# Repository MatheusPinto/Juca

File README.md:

---

---
Juca is an embedded mobile robotics board designed specifically for education. Juca combines affordability, expandability, and robust functionality, making it suitable for classroom and competition environments. Key features include modular hardware akin to Arduino shields, support for differential drive robots, and seamless integration with educational programming platforms.

This repository contains all the resources related to the development of the rover, 
including **firmware**, **software**, and **hardware** (electronics and mechanics). 

## 📂 Repository Structure

-   [docs/](docs/) - Project documentation
    
-   [firmware/](firmware/) - Microcontroller source code
    
-   [software/](software/) - PC applications, scripts, and simulations
    
-   [hardware/](hardware/) - Hardware design files
    
    -   [electronics/](hardware/electronics/) - Electronic design files
        
        -   [kicad/](hardware/electronics/kicad/) - Schematics and PCB layouts (KiCad project files)
            
        -   [bom/](hardware/electronics/bom/) - Bill of Materials
            
    -   [mechanics/](hardware/mechanics/) - Mechanical models (CAD, STL, STEP, drawings)
        
-   [tests/](tests/) - Integration tests (firmware + hardware + software)
    
-   [tools/](tools/) - Utility scripts and helper tools
    
-   [LICENSE](LICENSE) - License file
    
-   [README.md](README.md) - This file

## 📌 Reference

For information on the motivation, design objectives, and development criteria of the robot,  
please refer to the article *“Juca: an embedded mobile robotics board for education”*,  
published in the *16th Workshop on Robotics in Education (WRE 2025)*.

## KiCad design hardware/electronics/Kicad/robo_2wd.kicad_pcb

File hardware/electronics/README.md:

# Projeto Eletrônico do Juca

O Juca é a placa eletrônica propriamente dita, conforme observado na [Figura 1](#juca_board) e [Figura 2](#juca_board_back). Ela possui 180 mm x 125 mm, composta de duas camadas, com objetivo de ser robusta. 

<div id="juca_board" align="center">
  
  <br>
  <i>Figura 1: Visão 3D da parte superior da placa Juca.</i>
</div>

<br><br>

<div id="juca_board_back" align="center">
  
  <br>
  <i>Figura 2: Visão 3D da parte inferior da placa Juca.</i>
</div>

<br><br>

Na [Figura 3](#juca_diagram) é apresentado o diagrama de blocos do Juca. Serão apresentados cada módulo presente no sistema.

<br>

<div id="juca_diagram" align="center">
  
  <br>
  <i>Figura 3: Diagrama de blocos didático do sistema.</i>
</div>

---

## Microcontrolador (SoC)

O sistema utiliza o SoC **ESP32-S3-WROOM-1**, aproveitando suas capacidades de processamento dual-core e capacidade de comunicação por Wi-fi e BLE. O esquemático relacionado a esse módulo encontra-se na [Figura 4](#esp32_s3_sch).
O ESP32-S3 têm picos de consumo de corrente muito rápidos (especialmente ao ligar o Wi-Fi). Os capacitores (C11 e C12) próximos aos pinos de alimentação (`3V3`) filtram ruídos de alta frequência e evitam que a tensão caia momentaneamente, o que causaria resets inesperados.

<br>

<div id="esp32_s3_sch" align="center">
  
  <br>
  <i>Figura 4: Esquemático módulo ESP32-S3-WROOM-1.</i>
</div>

<br><br>

- **R13 (10k Pull-up no EN):** Mantém o pino de Enable (Reset) em nível alto (3.3V) para que o chip opere de maneira normal quando o pushbutton SW1 não for pressionado. O botão SW1, ao ser pressionado, aterra esse pino para resetar a MCU.

- **R14 (10k Pull-down no GPIO45):** Este é um **resistor de configuração (Strapping Pin)**. Ele garante que o pino 45 esteja em 0V durante o boot, informando ao ESP32-S3 que a memória Flash interna opera a **3.3V**. Sem ele, o chip poderia tentar alimentar a memória com 1.8V, impedindo a inicialização.

<br>

Toda gravação de firmware e comunicação com o chip é feita diretamente por meio da interface USB implementada diretamente no ESP32-S3 ([Figura 5](#usb_sch)), através dos pinos GPIO19 (DEBUG_DM) e GPIO20 (DEBUG_DP).

<br>

<div id="usb_sch" align="center">
  
  <br>
  <i>Figura 5: Interface USB de conexão com o ESP32-S3.</i>
</div>

---

## Alimentação

O hardware possui três barramentos principais de alimentação ([Figura 7](#power_sch)):

1.  **+BATT (Potência):** 6V a 12V para os motores e alimentação geral do sistema. Essa alimentação pode advir de uma bateria (por meio do conector J3) ou de uma fonte CC externa conectada por um por jack-cc (J4). Um interruptor (SW3) é responsável por conectar a bateria/fonte ao restante da placa. Se bateria e fonte estiver conectadas no sistema, a fonte externa poderá carregar a bateria. Note que a placa não possui BMS, dessa forma será necessário utilizar no próprio pack de bateria um BMS.

2. **5V (Lógica):** Gerado por um conversor *buck* bastante utilizado em projetos de eletrônica hobistas (Figura) ou pela interface USB ([Figura 6](#buck_il_2825)). Cria uma barramento de 5V para alimentar dispositivos externos, e para alimentar o driver de motor e o sensores ultrassônicos. Se alimentação vier do USB (sem fonte +BATT), o driver de motor é acionado, mas os motores não.

<div id="buck_il_2825" align="center">
  
  <br>
  <i>Figura 6: Mini placa para buck IL 2825.</i>
</div>

<br>

3.  **3.3V (Lógica):** Gerado por um regulador LDO (como o AMS1117) para alimentar o ESP32-S3 e o restantes dos sensores.

<br>

<div id="power_sch" align="center">
  
  <br>
  <i>Figura 7: Módulos de alimentação da placa.</i>
</div>

---
## *Driver* de motores

Para acionamento dos motores por meio do PWM, utilizou-se o chip L298N. Esse módulo possui uma ponte H para controle de direção e amplificação da potência nos motores. Um diagrama do circuito do L298N retirado do seu datasheet é apresentado na [Figura 8](#l298N). O esquemático do driver desenvolvido com o chip é apresentado na [Figura 9](#mot_driver_sch).

<br>

<div id="l298N" align="center">
  
  <br>
  <i>Figura 8: Diagrama do circuito interno do L298N.</i>
</div>

<br><br>

<div id="mot_driver_sch" align="center">
  
  <br>
  <i>Figura 9: Esquemático do circuito driver de motor do Juca.</i>
</div>

<br><br>

A placa foi pensada usando um motor com as seguintes especificações (mas facilmente adaptado para outros tipos de motor, mudando valores de tensão de alimentação da bateria e/ou mudando alguns valores de resistores no circuito de sensor de corrente):

|**Parâmetro**|**Valor / Especificação**|
|---|---|
|**Tensão de Operação**|6V DC|
|**Velocidade (Sem Carga)**|280 RPM|
|**Máxima Eficiência**|2.0 kg.cm @ 170 RPM|
|**Potência na Máx. Eficiência**|2.0 W|
|**Corrente na Máx. Eficiência**|0.60 A|
|**Torque de Partida (Stall)**|5.2 kg.cm @ 110 RPM|
|**Potência Máxima**|3.1 W|
|**Corrente de Pico (Stall)**|1.10 A|
|**Diâmetro do Motor**|25 mm|
|**Comprimento Total (Corpo + Eixo)**|73 mm|
|**Diâmetro do Eixo**|4 mm|
|**Comprimento do Eixo**|12 mm|

<br>

O motor utilizado a priori é daqueles se acham facilmente em lojas online de materiais eletrônicos, possuindo integrado um *encoder* de quadratura a efeito hall, conforme [Figura 10](#motor_wire)

<br>

<div id="motor_wire" align="center">
  
  <br>
  <i>Figura 10: Motor com encoder utilizado.</i>
</div>

<br>

Com base nas combinações dos pinos MOT_IN1, MOT_IN2, MOT_IN3 e MOT_IN4, pode-se determinar o controle de direção e velocidades das rodas. Note que quando todos os pinos estiverem em ALTO, as rodas irão travar eletronicamente, pois as portas lógicas SUPERIORES do driver ([Figura 8](#l298N)) irão forçar os polos do motor ao mesmo potencial elétrico (Vcc). Da mesma forma, quando todos os pinos estiverem em BAIXO, as rodas irão travar eletronicamente, pois as portas lógicas INFERIORES do driver ([Figura 8](#l298N)) irão forçar os polos do motor ao mesmo potencial elétrico (GND). Infelizmente, nesse projeto não há possibilidade de deixar as rodas em ponto morto, sem torque (deixar as rodas desconectadas), pois os pinos de habilitação (EnA e EnB) foram deixadas diretamente conectadas do +3V3.

<br>

| **Direção Desejada**  | **MOT_IN1** | **MOT_IN2** | **MOT_IN3** | **MOT_IN4** | **Efeito Prático**                       |
| --------------------- | ----------- | ----------- | ----------- | ----------- | ---------------------------------------- |
| **Frente**            | PWM         | Low         | PWM         | Low         | Ambas as rodas giram para frente         |
| **Trás**              | Low         | PWM         | Low         | PWM         | Ambas as rodas giram para trás           |
| **Girar p/ Direita**  | PWM         | Low         | Low         | PWM         | Roda esquerda p/ frente, direita p/ trás |
| **Girar p/ Esquerda** | Low         | PWM         | PWM         | Low         | Roda direita p/ frente, esquerda p/ trás |
| **Curva p/ Direita**  | PWM         | Low         | Low         | Low         | Apenas roda esquerda gira                |
| **Curva p/ Esquerda** | Low         | Low         | PWM         | Low         | Apenas roda direita gira                 |
| **Freio (Ativo)**     | Low         | Low         | Low         | Low         | Motores travam eletronicamente           |
| **Freio (Ativo)**     | High        | High        | High        | High        | Motores travam eletronicamente           |

<br>

Além do acionamento dos motores, o módulo de driver de motores fornece a corrente dos motores por meio de dois pinos SENSE_A e SENSE_B. Essas correntes são aplicadas a resistores de *shunt* de 0,1 Ohm PTH do tipo filme de carbono de 2 Watts (no limiar de potência para os motores), por serem fáceis de serem achadas comercialmente no Brasil. Sabendo a resistência dos *shunts* e medindo a tensão dos mesmos por meio de do ADC no SoC, aplica-se a Lei de Ohm e se obtém a corrente.. Posto isto, os valores de queda de tensão que surgem nesses resistores são muito pequenos, devendo ser necessário um circuito de amplificação (que será abordado posteriormente). 

O módulo também possui uma interface para entrada de encoders de quadratura. Essa parte será abordada mais adiante também, pois também serão apresentados os encoders utilizados. 

---
## Sensor de corrente dos motores

Para monitorar a carga dos motores e detectar obstáculos ou travamentos (stall), o projeto utiliza um circuito de amplificação baseado no AmpOp **LM324A** ([Figura 11](#curr_sense_sch)). O circuito utiliza a queda de tensão sobre os resistores de shunt (R1​ e R2​ de 0.1Ω em [Figura 9](#mot_driver_sch)) localizados nos pinos de _Sense_ do driver L298N. Como essa tensão é muito baixa para uma leitura precisa pelo ADC, aplicamos um **Amplificador Não-Inversor** a cada uma delas.

<br>

<div id="curr_sense_sch" align="center">
  
  <br>
  <i>Figura 11: Esquemático do circuito de medição de corrente dos motores.</i>
</div>

<br><br>

O ganho dos amplificadores foi determinado de tal forma que a corrente máxima de torque dos motores que foram utilizados (1,1 A) fosse próxima dos 3 V, já que o ADC do ESP32-S3 possui fundo de escala de 3V3. Como o LM324 não é rail-to-rail, ele satura cerca de 1.5V abaixo do VCC​, com 5V de alimentação, a saída máxima real será de aproximadamente **3.5V**. o suficiente para a aplicação. Para tanto, o cálculo usando o amplificador não inversor foi:

$$G=1+R_{in}​.R_{feedback​}​=1+3k.82k​≈28,33.$$

<br>
Abaixo está uma tabela ilustrativa com exemplos de tensão e leitura do ADC.
<br>

| **Corrente do Motor** | **Tensão no Shunt** | **Saída do AmpOp** | **Valor no ADC (10-bit)** | **Status do Motor** |
| --------------------- | ------------------- | ------------------ | ------------------------- | ------------------- |
| $0.1\text{A}$         | $0.01\text{V}$      | $0.28\text{V}$     | $\approx 87$              | Sem carga           |
| $0.6\text{A}$         | $0.06\text{V}$      | $1.70\text{V}$     | $\approx 527$             | Eficiência Máxima   |
| **$1.1\text{A}$**     | **$0.11\text{V}$**  | **$3.11\text{V}$** | **$\approx 965$**         | **Stall (Travado)** |
<br>
Na saída do amplificador é colocado um filtro passa-baixa RC (150Ω e 1μF) para eliminar ruídos de chaveamento (PWM), e um diodo Zener de 3.3V para garantir que a saída nunca ultrapasse o limite do pino analógico do microcontrolador.

---
## *Encoders*

O Juca é capaz de receber os dois sinais advindos de um encoder incremental de quadratura. Isso é importante no cálculo de odometria do robô, onde é possível determinar o deslocamento angular da roda com base nos pulsos dos sinais gerados pelo encoder.

O encoder é acoplado à roda, que possui algum tipo de disco magnético (ou óptico) multi-polar que gira solidário ao eixo do motor.

Os sinais gerados pelo encoder são geralmente denominados Fase A e Fase B. De forma básica, existem dois sensores que medem a variação do campo magnético (ou a passagem de luz) e geram ondas quadradas defasadas entre si em 90°. Essa defasagem é o que permite ao sistema identificar não apenas a velocidade, mas também o sentido de rotação (horário ou anti-horário), dependendo de qual fase sofre a transição de nível primeiro (ver [Figura 12](#quad_enc_anima) e [Figura 13](#encoder_wave)).

<br><br>

<div id="quad_enc_anima" align="center">
  
  <br>
  <i>Figura 12: Ilustração do comportamento de um encoder de quadratura.</i>
</div>

<br>

<div id="encoder_wave" align="center">
  
  <br>
  <i>Figura 13: Comportamento do encoder para o sentido direto e reverso da roda.</i>
</div>

<br>
<br>

O encoder utilizado primariamente no Juca é o do motor apresentado na [Figura 10](#motor_wire), e possui os seguintes parâmetros:

| **Parâmetro**            | **Detalhe / Valor**                      |
| ------------------------ | ---------------------------------------- |
| **Relação de Redução**   | 1:34 (Exato: 1:34.02)                    |
| **Resolução do Encoder** | 341.2 PPR (Pulsos por Revolução da Roda) |
| **Cálculo da Resolução** | 11 pulsos (motor) x 34.02 (redução)      |
| **Comprimento Total**    | 73 mm (incluindo motor e eixo)           |

O motor elétrico gira muito rápido, mas com pouca força (torque). Por isso, ele possui uma **caixa de engrenagens** acoplada.

- **O que significa:** O motor interno precisa dar **34,02 voltas** completas para que a roda do robô dê apenas **1 volta**.
- **Vantagem:** Isso aumenta o torque do motor em 34 vezes, permitindo que o robô carregue peso e vença a inércia, além de reduzir a velocidade para algo controlável (280 RPM).

O encoder está montado no eixo do motor (antes da redução). O sensor lê **11 pulsos** a cada volta do motor interno.

- **O cálculo:** Como a roda só gira uma vez a cada 34,02 voltas do motor, multiplicamos: 11×34,02=341,22.
- **PPR (Pulsos por Revolução):** Este é o número que seu código usa para saber que o robô completou uma volta de roda. Se o microcontrolador contou 341 pulsos, o robô percorreu quase que exatamente uma distância igual à circunferência da sua roda.

Para saber como o ESP32-S3 trabalha com os pulsos de encoders acesse este conteúdo.

---
## Sensores de linha IR

O módulo de sensores de linha IR não está presente diretamente na placa, devido às demandas de restrições geométricas necessárias para acomoda-la (geralmente longe da placa e em posições diversas de acordo com a necessidade do robô). Dessa forma, o Juca oferece uma interface para 5 sensores IR ([Figura 15](#ir_line_sch)).

<br>

<div id="ir_line_sch" align="center">
  
  <br>
  <i>Figura 14: Jumpers para interface com sensores de linha IR.</i>
</div>

<br>

Inicialmente utilizamos o módulo apresentado na [Figura 15](#ir_module). 

<br>

<div id="ir_module" align="center">
  
  <br>
  <i>Figura 15: Módulo IR utilizado no Juca.</i>
</div>

<br>

Na [Figura 16](#juca_ir_sensor) é possível visualizar como este módulo pode ser alocado na parte inferior de um possível chassi para o Juca, e quais posições podem ser escolhidas para cada pino de forma a detectar onde está posicionada uma linha no chão.

<br>

<div id="juca_ir_sensor" align="center">
  
  <br>
  <i>Figura 16: Desenho representativo do módulo IR abaixo de um chassi hipotético para o Juca e possíveis posições de detecção e pinos utilizados.</i>
</div>

<br>

Para esse módulo é recomendada uma largura de linha de aproximadamente 20 mm.

---
## Sensores de distância ultrassônicos

O Juca possui uma interface para conexão com três dispositivos de detecção de obstáculos por ondas ultrassônicas. A interface criada pode ser observada no esquemático da [Figura 16](#hc_sr04_sch).

<br>

<div id="hc_sr04_sch" align="center">
  
  <br>
  <i>Figura 17: Esquemático da interface de conexão com os módulos ultrassônicos.</i>
</div>

<br>

Os dispositivos ultrassônicos pensados para serem utilizados no Juca são do modelo HC-SR04 ([Figura 17](#hc_sr04)). Apesar disso, existem outros modelos no mercado com a mesma interface, que poderiam ser utilizadas no lugar. O ângulo de alcance de cada  HC-SR04 é aproximadamente 15 graus, tomando como origem o centro do transdutor de ondas.

<br>

<div id="hc_sr04" align="center">
  
  <br>
  <i>Figura 18: Módulo HC-SR04.</i>
</div>

<br>

Conforme pode ser observado na [Figura 18](#ultrasonic_detect), além da alimentação, o HC-SR04 possui um pino de gatilho e um pino de eco. O pino de gatilho tem por função a recepção de um pulso com duração aproximada de 10 𝜇s gerada pelo microcontrolador por meio de GPIO. Após geração do pulso, uma onda ultrassônica de 40 kHz é liberada pelo atuador por um período de 200 𝜇s. A presença de um objeto no caminho da onda irá refleti-la como um eco na direção do sensor. No pino de eco será gerado um pulso com largura $T_{onda}$ igual ao intervalo entre geração da onda e captação do eco. Este pulso irá variar entre 150 𝜇s e 25 ms caso um objeto seja detectado, sendo 38 ms caso nenhum obstáculo seja atingido. A distância 𝑑 do transdutor ao obstáculo é dada pela seguinte equação:

$$\begin{equation}
d = \frac{v_{som} \cdot T_{onda}}{2} 
\label{eq_ultrasonic}
\end{equation}$$

onde $v_{som}$ corresponde à velocidade do som no meio. Note que $T_{onda}/2$ corresponde ao tempo necessário para que a onda percorra o caminho entre o transdutor e o objeto – tempo relativo ao sinal gerado atingir o objeto, ou do eco atingir o sensor. Considerando como meio o ar em temperatura próxima aos 20 graus C, então  $v_{som}$ = 343 𝑚/𝑠 (HALLIDAY et al., 2013). Dessa forma, a distância do objeto pode variar entre 2,6 cm e 430 cm. Como a tensão nominal do HC-SR04 é 5 V, ele aceita sinal de 3V3 no pino de gatilho, mas o sinal gerado pelo eco é 5V. Por isso a interface no Juca utiliza um conversor de nível lógico (*level_shifter*).

<br>

<div id="ultrasonic_detect" align="center">
  
  <br>
  <i>Figura 19: Ilustração do comportamento de detecção de objetos com o HC-SR04.</i>
</div>

<br>

---
## IMU

Os encoders são adequados em baixas frequências (estáticos/movimentos lentos). Uma Unidade de Medição Inercial - *Inertial Measurement Unit* (IMU) é adequada para capturar mudanças bruscas e rápidas (alta frequência). Ao aplicar um filtro EKF podemos combinar as duas fontes de dados, filtrando o ruído individual de cada sensor para gerar uma estimativa de pose muito mais robusta.

Uma IMU é composta basicamente por dois sensores independentes: um acelerômetro (mede  aceleração linear) e um giroscópio (mede aceleração angular). O IMU utilizado no Juca é o MPU-6050, possuindo 6 graus de liberdade (6 DoF). Isso quer dizer quer ele é capaz de medir aceleração linear em 3 direções (XYZ) e angular em 3 direções (XYZ). Foi utilizado um módulo pronto para o MPU-6050, denominado frequentemente de ITG/MPU. Uma foto dessa placa, com uma representação dos eixos coordenados no corpo e o sentido do ângulos, podem ser observados na [Figura 20](#mpu6050_gyro).

<br>

<div id="mpu6050_gyro" align="center">
  
  <br>
  <i>Figura 20: Uma foto a placa ITG/MPU (MPU-6050), com uma representação dos eixos coordenados no corpo e o sentido do ângulos.</i>
</div>

<br>

No Juca, o CI está localizado dentro da área do módulo de expansão ([Figura 1](#juca_board)). Os pinos utilizados podem ser visualizados na [Figura 21](#imu_sch).

<br>

<div id="imu_sch" align="center">
  
  <br>
  <i>Figura 21: Esquemático do MPU-6050 no Juca.</i>
</div>

<br>

Seguem algumas especificações pertinentes:

|**Categoria**|**Parâmetro**|**Detalhes / Valor**|
|---|---|---|
|**Alimentação**|Tensão de Operação (VCC)|**3.3V** (Conforme indicado no pino 8)|
|**Comunicação**|Protocolo de Interface|**I2C** (Pinos SCL e SDA) compartilhados nos pinos de expansão|
|**Pinagem (I2C)**|Clock / Dados|**Pino 6 (SCL)** e **Pino 5 (SDA)**|
|**Interrupção**|Sinal de Saída|**Pino 1 (INT)** - Conectado à linha `IMU_INT`|
|**Resolução**|ADC (Conversor Analógico-Digital)|**16 bits** por canal|
|**Giroscópio**|Fundo de Escala (Configurado)|**500°/s** (Escalas de ±250, 500, 1000, 2000°/s)|
|**Acelerômetro**|Eixos de Medição|**3 eixos** (X, Y, Z)|
|**Endereço I2C**|Seleção de Endereço (AD0)|**Pino 2 (AD0)** - Não utilizados (NC)|
|**Expansão**|Interface Auxiliar|**Pinos 3 (XCL) e 4 (XDA)** - Não utilizados (NC)|

---
## Interface de expansão

---
## Mapeamento de pinos (Pinout)

### Controle de motores, *encoders* e sensores de corrente

| Recurso         | Pino (GPIO) | Tipo/Interface  | Descrição                            |
| --------------- | ----------- | --------------- | ------------------------------------ |
| **MOT_IN1**     | GPIO11      | Saída (PWM)     | Motor esquerdo - sentido A           |
| **MOT_IN2**     | GPIO10      | Saída (PWM)     | Motor esquerdo - sentido B           |
| **MOT_IN3**     | GPIO13      | Saída (PWM)     | Motor direito - sentido A            |
| **MOT_IN4**     | GPIO12      | Saída (PWM)     | Motor direito - sentido B            |
| **ENC1_A**      | GPIO7       | Entrada PCNT    | Encoder motor direito - canal A      |
| **ENC1_B**      | GPIO6       | Entrada PCNT    | Encoder motor direito - canal B      |
| **ENC2_A**      | GPIO14      | Entrada PCNT    | Encoder motor esquerdo - canal A     |
| **ENC2_B**      | GPIO21      | Entrada PCNT    | Encoder motor esquerdo - canal B     |
| **CURR_LM_ADC** | GPIO2       | Analógico (ADC) | Leitura de corrente - motor esquerdo |
| **CURR_RM_ADC** | GPIO9       | Analógico (ADC) | Leitura de corrente - motor direito  |
### Sensores ultrassônicos

| Recurso         | Pino (GPIO) | Tipo/Interface               | Descrição                                                 |
| --------------- | ----------- | ---------------------------- | --------------------------------------------------------- |
| **SONAR_TRIG**  | GPIO42      | Saída Digital                | Gatilho para todos os sensores ultrassônicos (barramento) |
| **SONAR0_ECHO** | GPIO1       | Entrada (captura de entrada) | Pino de eco do sensor ultra. dir.                         |
| **SONAR1_ECHO** | GPIO4       | Entrada (captura de entrada) | Pino de eco do sensor ultra. centro                       |
| **SONAR2_ECHO** | GPIO5       | Entrada (captura de entrada) | Pino de eco do sensor ultra. esq.                         |
### Sensores de linha IR

| Recurso             | Pino (GPIO) | Tipo/Interface | Descrição                               |
| ------------------- | ----------- | -------------- | --------------------------------------- |
| **IR_LEFT**         | GPIO25      | Digital        | Sensor de Linha / Obstáculo esquerda    |
| **IR_CENTER_LEFT**  | GPIO33      | Digital        | Sensor de Linha / Obstáculo centro esq. |
| **IR_MIDDLE**       | GPIO32      | Digital        | Sensor de Linha / Obstáculo centro      |
| **IR_CENTER_RIGHT** | GPIO35      | Digital        | Sensor de Linha / Obstáculo centro dir. |
| **IR_RIGHT**        | GPIO34      | Digital        | Sensor de Linha / Obstáculo direita     |

### IMU

| Recurso     | Pino (GPIO) | Tipo/Interface | Descrição                             |
| ----------- | ----------- | -------------- | ------------------------------------- |
| **MCU_SDA** | GPIO40      | I2C            | Dados Barramento I2C (IMU / Expansão) |
| **MCU_SCL** | GPIO39      | I2C            | Clock Barramento I2C (IMU / Expansão) |
| **IMU_INT** | GPIO41      | Entrada/IRQ    | Interrupção da IMU (MPU-6050)         |

### Expansão (pinos sobressalentes para conexão de outros módulos externos)

| Pino (GPIO)  | Pino (GPIO) | Pino (GPIO) | Pino (GPIO) | Pino (GPIO)  |
| ------------ | ----------- | ----------- | ----------- | ------------ |
| GPIO3        | GPIO35      | GPIO36      | GPIO37      | GPIO38       |
| GPIO45       | GPIO46      | GPIO47      | GPIO48      | SDA (GPIO40) |
| SCL (GPIO39) | TXD0        | RXD0        |             |              |

---

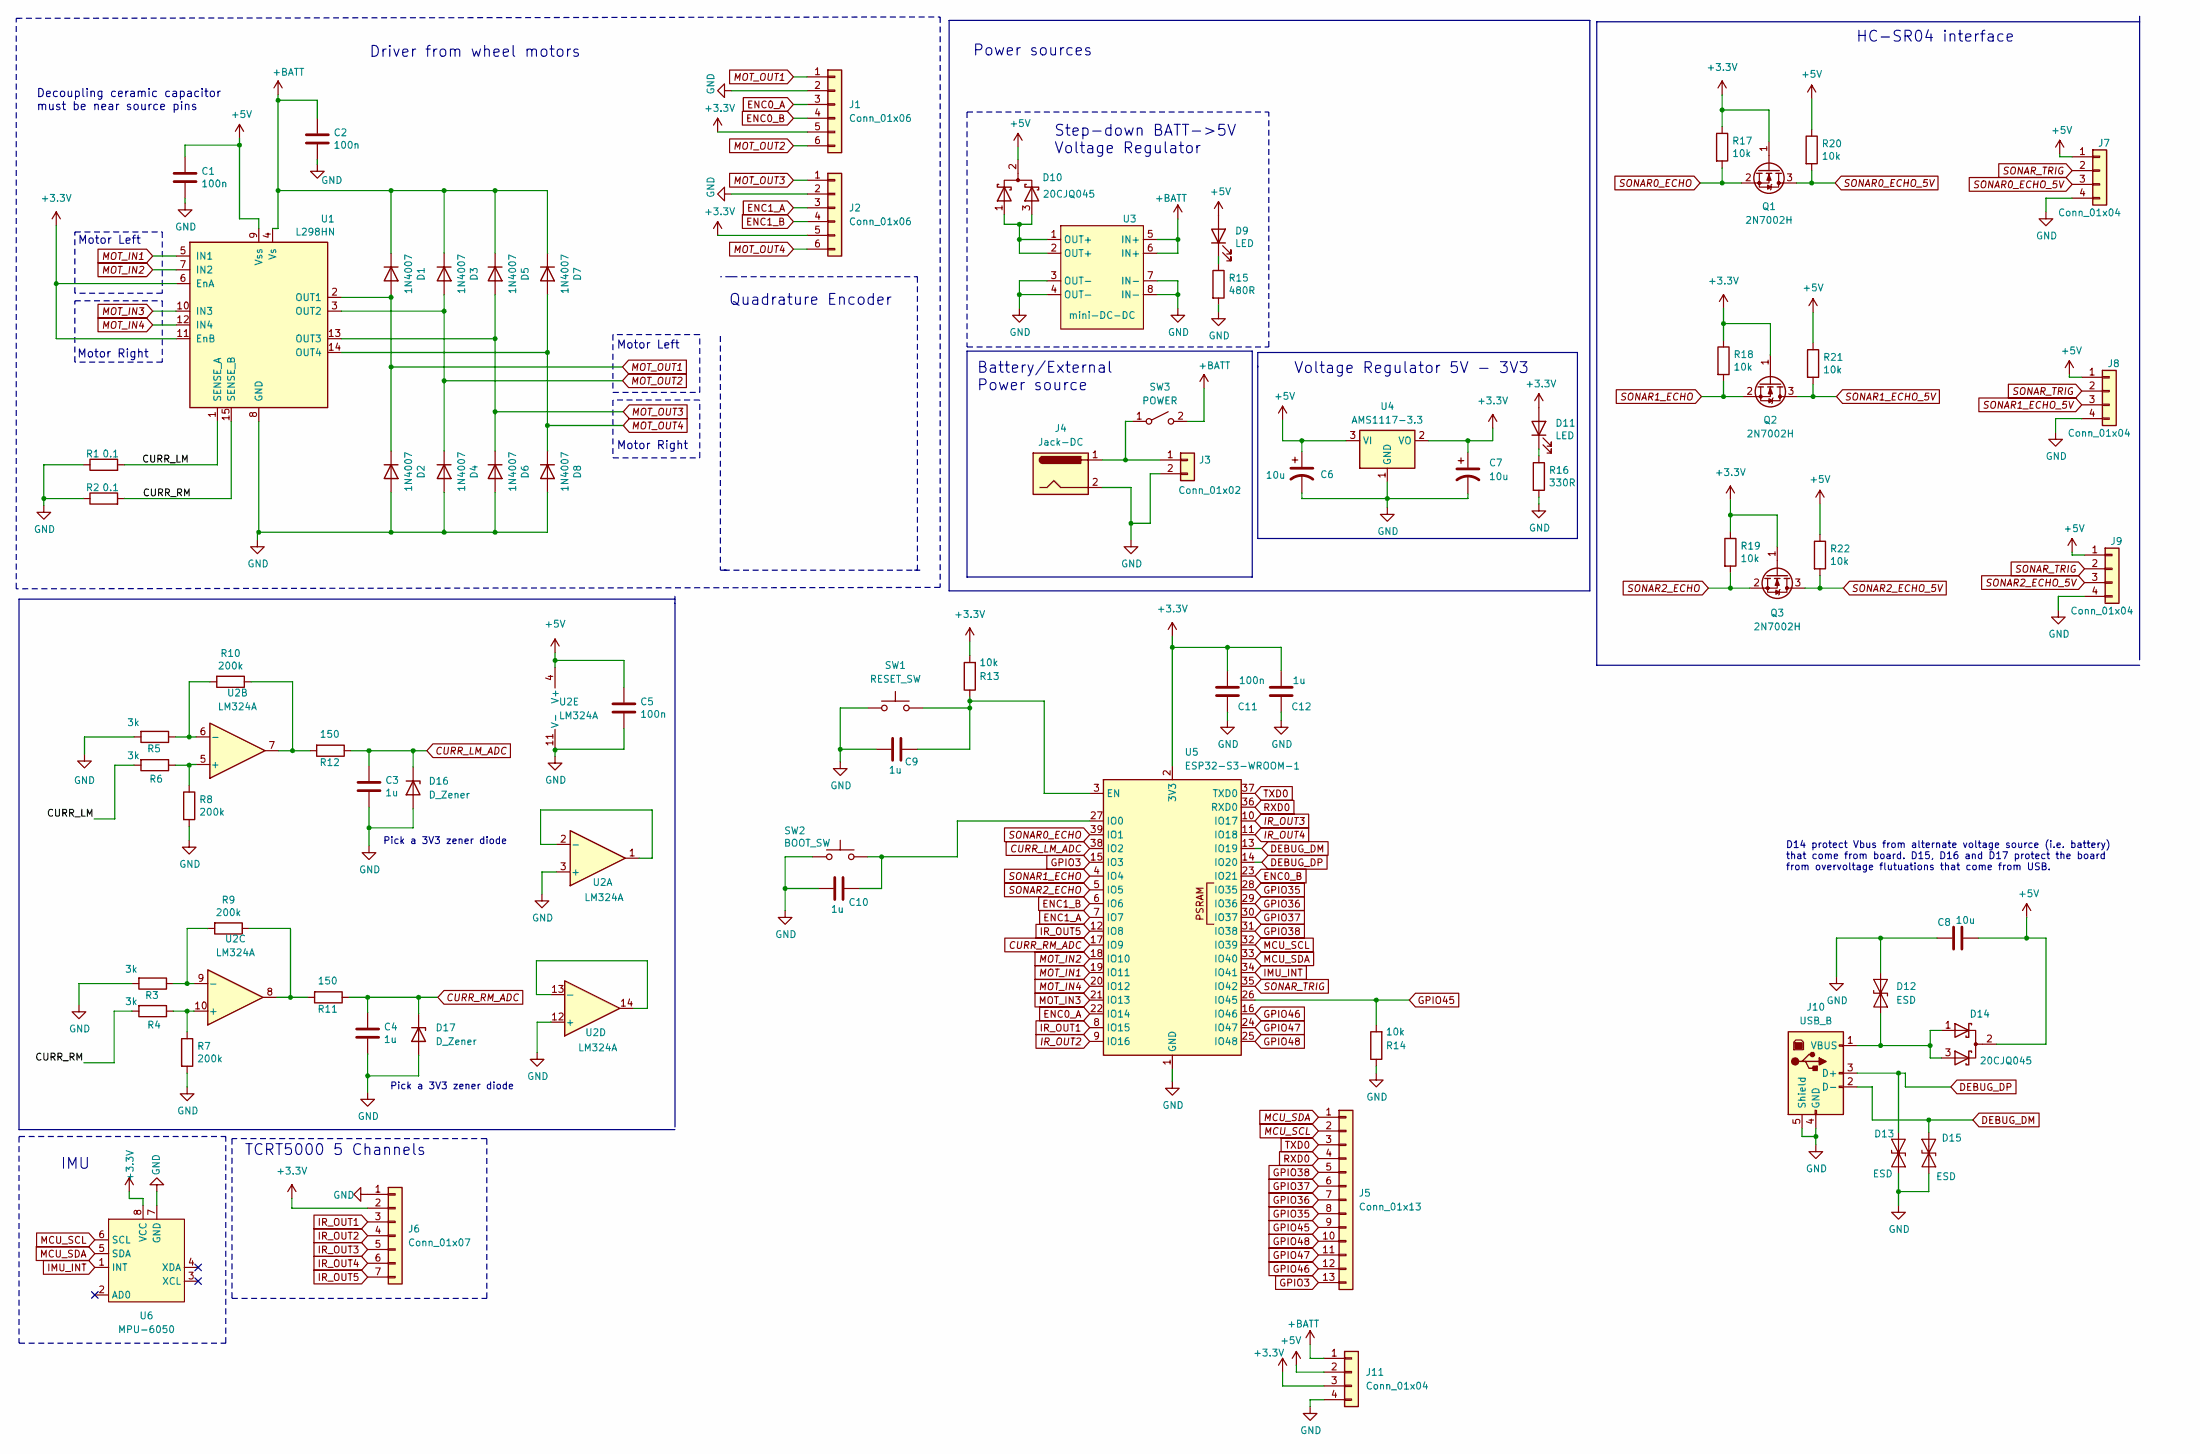
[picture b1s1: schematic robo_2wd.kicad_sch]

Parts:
C1, C2: 100n; CP_Elec_8x10
C3, C4, C9, C10, C12: 1u; C_0805_2012Metric_Pad1.18x1.45mm_HandSolder
C5, C11: 100n; C_0805_2012Metric_Pad1.18x1.45mm_HandSolder
C6, C7: 10u; CP_EIA-6032-28_Kemet-C_Pad2.25x2.35mm_HandSolder
C8: 10u; C_0805_2012Metric_Pad1.18x1.45mm_HandSolder
D1, D2, D3, D4, D5, D6, D7, D8: 1N4007; D_SMA
D9, D11: LED; LED_0603_1608Metric_Pad1.05x0.95mm_HandSolder
D10, D14: 20CJQ045; SOT-223-3_TabPin2
D12, D13, D15: ESD; D_SOD-523
D16, D17: D_Zener; D_MiniMELF
J1, J2: Conn_01x06; Molex_KK-254_AE-6410-06A_1x06_P2.54mm_Vertical
J3: Conn_01x02; Molex_KK-254_AE-6410-02A_1x02_P2.54mm_Vertical
J4: Jack-DC; Jack_J4_ 2_1mm_vertical
J5: Conn_01x13; PinHeader_1x13_P2.54mm_Vertical
J6: Conn_01x07; Molex_KK-254_AE-6410-07A_1x07_P2.54mm_Vertical
J7, J8, J9: Conn_01x04; Molex_KK-254_AE-6410-04A_1x04_P2.54mm_Vertical
J10: USB_B; USB_B_TE_5787834_Vertical
J11: Conn_01x04; PinHeader_1x04_P2.54mm_Vertical
Q1, Q2, Q3: 2N7002H; SOT-23
R1, R2: 0.1; R_Axial_DIN0516_L15.5mm_D5.0mm_P7.62mm_Vertical
R3, R4, R5, R6: 3k; R_1206_3216Metric_Pad1.30x1.75mm_HandSolder
R7, R8, R9, R10: 200k; R_1206_3216Metric_Pad1.30x1.75mm_HandSolder
R11, R12: 150; R_0603_1608Metric_Pad0.98x0.95mm_HandSolder
R13, R14, R17, R18, R19, R20, R21, R22: 10k; R_0603_1608Metric_Pad0.98x0.95mm_HandSolder
R15: 480R; R_0603_1608Metric_Pad0.98x0.95mm_HandSolder
R16: 330R; R_0603_1608Metric_Pad0.98x0.95mm_HandSolder
SW1: RESET_SW; SW_SPST_PTS645
SW2: BOOT_SW; SW_SPST_PTS645
SW3: POWER; ToggleSwitch_MTS-102_SPDT
U1: L298HN; TO-220-15_P2.54x2.54mm_StaggerOdd_Lead4.58mm_Vertical
U2: LM324A; SOIC-14_3.9x8.7mm_P1.27mm
U3: mini-DC-DC
U4: AMS1117-3.3; SOT-223-3_TabPin2
U5: ESP32-S3-WROOM-1
U6: MPU-6050; mpu6050_module

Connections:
+3.3V: C7.1, C11.1, C12.1, D11.2 (A), J1.5, J2.5, J6.2, J11.3, Q1.1 (G), Q2.1 (G), Q3.1 (G), R13.2, R17.1, R18.1, R19.1, U1.6 (EnA), U1.11 (EnB), U4.2 (VO), U5.2 (3V3), U6.8 (VCC)
+5V: C1.1, C5.1, C6.1, C8.2, D9.2 (A), D10.2 (A), D14.2 (A), J7.1, J8.1, J9.1, J11.2, R20.1, R21.1, R22.1, U1.9 (Vss), U2.4 (V+), U4.3 (VI)
+BATT: C2.1, D1.1 (K), D3.1 (K), D5.1 (K), D7.1 (K), J11.1, SW3.2 (B), U1.4 (Vs), U3.5 (IN+), U3.6 (IN+)
/CURR_LM: R1.2, R6.2, U1.1 (SENSE_A)
/CURR_RM: R2.2, R4.2, U1.15 (SENSE_B)
CURR_LM_ADC: C3.1, D16.1 (K), R12.1, U5.38 (IO2)
CURR_RM_ADC: C4.1, D17.1 (K), R11.1, U5.17 (IO9)
DEBUG_DM: D15.2 (A2), J10.2 (D-), U5.13 (IO19)
DEBUG_DP: D13.2 (A2), J10.3 (D+), U5.14 (IO20)
ENC0_A: J1.3, U5.22 (IO14)
ENC0_B: J1.4, U5.23 (IO21)
ENC1_A: J2.3, U5.7 (IO7)
ENC1_B: J2.4, U5.6 (IO6)
GND: C1.2, C2.2, C3.2, C4.2, C5.2, C6.2, C7.2, C8.1, C9.1, C10.1, C11.2, C12.2, D2.2 (A), D4.2 (A), D6.2 (A), D8.2 (A), D12.2 (A2), D13.1 (A1), D15.1 (A1), D16.2 (A), D17.2 (A), J1.2, J2.2, J3.2, J4.2, J6.1, J7.4, J8.4, J9.4, J10.4 (GND), J10.5 (Shield), J11.4, R1.1, R2.1, R3.2, R5.2, R7.2, R8.2, R14.1, R15.2, R16.2, SW1.1, SW2.1, U1.8 (GND), U2.3 (+), U2.11 (V-), U2.12 (+), U3.3 (OUT-), U3.4 (OUT-), U3.7 (IN-), U3.8 (IN-), U4.1 (GND), U5.1 (GND), U5.40 (GND), U5.41 (GND), U6.7 (GND)
GPIO3: J5.13, U5.15 (IO3)
GPIO35: J5.8, U5.28 (IO35)
GPIO36: J5.7, U5.29 (IO36)
GPIO37: J5.6, U5.30 (IO37)
GPIO38: J5.5, U5.31 (IO38)
GPIO45: J5.9, R14.2, U5.26 (IO45)
GPIO46: J5.12, U5.16 (IO46)
GPIO47: J5.11, U5.24 (IO47)
GPIO48: J5.10, U5.25 (IO48)
IMU_INT: U5.34 (IO41), U6.1 (INT)
IR_OUT1: J6.3, U5.8 (IO15)
IR_OUT2: J6.4, U5.9 (IO16)
IR_OUT3: J6.5, U5.10 (IO17)
IR_OUT4: J6.6, U5.11 (IO18)
IR_OUT5: J6.7, U5.12 (IO8)
MCU_SCL: J5.2, U5.32 (IO39), U6.6 (SCL)
MCU_SDA: J5.1, U5.33 (IO40), U6.5 (SDA)
MOT_IN1: U1.5 (IN1), U5.19 (IO11)
MOT_IN2: U1.7 (IN2), U5.18 (IO10)
MOT_IN3: U1.10 (IN3), U5.21 (IO13)
MOT_IN4: U1.12 (IN4), U5.20 (IO12)
MOT_OUT1: D1.2 (A), D2.1 (K), J1.1, U1.2 (OUT1)
MOT_OUT2: D3.2 (A), D4.1 (K), J1.6, U1.3 (OUT2)
MOT_OUT3: D5.2 (A), D6.1 (K), J2.1, U1.13 (OUT3)
MOT_OUT4: D7.2 (A), D8.1 (K), J2.6, U1.14 (OUT4)
unnamed: D9.1 (K), R15.1
unnamed: D10.1 (K), D10.3 (K), U3.1 (OUT+), U3.2 (OUT+)
unnamed: D11.1 (K), R16.1
unnamed: D12.1 (A1), D14.1 (K), D14.3 (K), J10.1 (VBUS)
unnamed: J3.1, J4.1, SW3.1 (A)
unnamed: R10.1, R12.2, U2.7
unnamed: R9.1, R11.2, U2.8
unnamed: U2.1, U2.2 (-)
unnamed: R6.1, R8.1, U2.5 (+)
unnamed: R5.1, R10.2, U2.6 (-)
unnamed: R4.1, R7.1, U2.10 (+)
unnamed: R3.1, R9.2, U2.9 (-)
unnamed: U2.13 (-), U2.14
unnamed: C9.2, R13.1, SW1.2, U5.3 (EN)
unnamed: C10.2, SW2.2, U5.27 (IO0)
RXD0: J5.4, U5.36 (RXD0)
SONAR0_ECHO: Q1.2 (S), R17.2, U5.39 (IO1)
SONAR0_ECHO_5V: J7.3, Q1.3 (D), R20.2
SONAR1_ECHO: Q2.2 (S), R18.2, U5.4 (IO4)
SONAR1_ECHO_5V: J8.3, Q2.3 (D), R21.2
SONAR2_ECHO: Q3.2 (S), R19.2, U5.5 (IO5)
SONAR2_ECHO_5V: J9.3, Q3.3 (D), R22.2
SONAR_TRIG: J7.2, J8.2, J9.2, U5.35 (IO42)
TXD0: J5.3, U5.37 (TXD0)

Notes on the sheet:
D14 protect Vbus from alternate voltage source (i.e. battery) that come from board. D15, D16 and D17 protect the board from overvoltage flutuations that come from USB.
Driver from wheel motors
Motor Right
Voltage Regulator 5V - 3V3
Decoupling ceramic capacitor must be near source pins
Power sources
Motor Left
Pick a 3V3 zener diode
IMU
Battery/External Power source
TCRT5000 5 Channels
Quadrature Encoder
HC-SR04 interface
Step-down BATT->5V Voltage Regulator

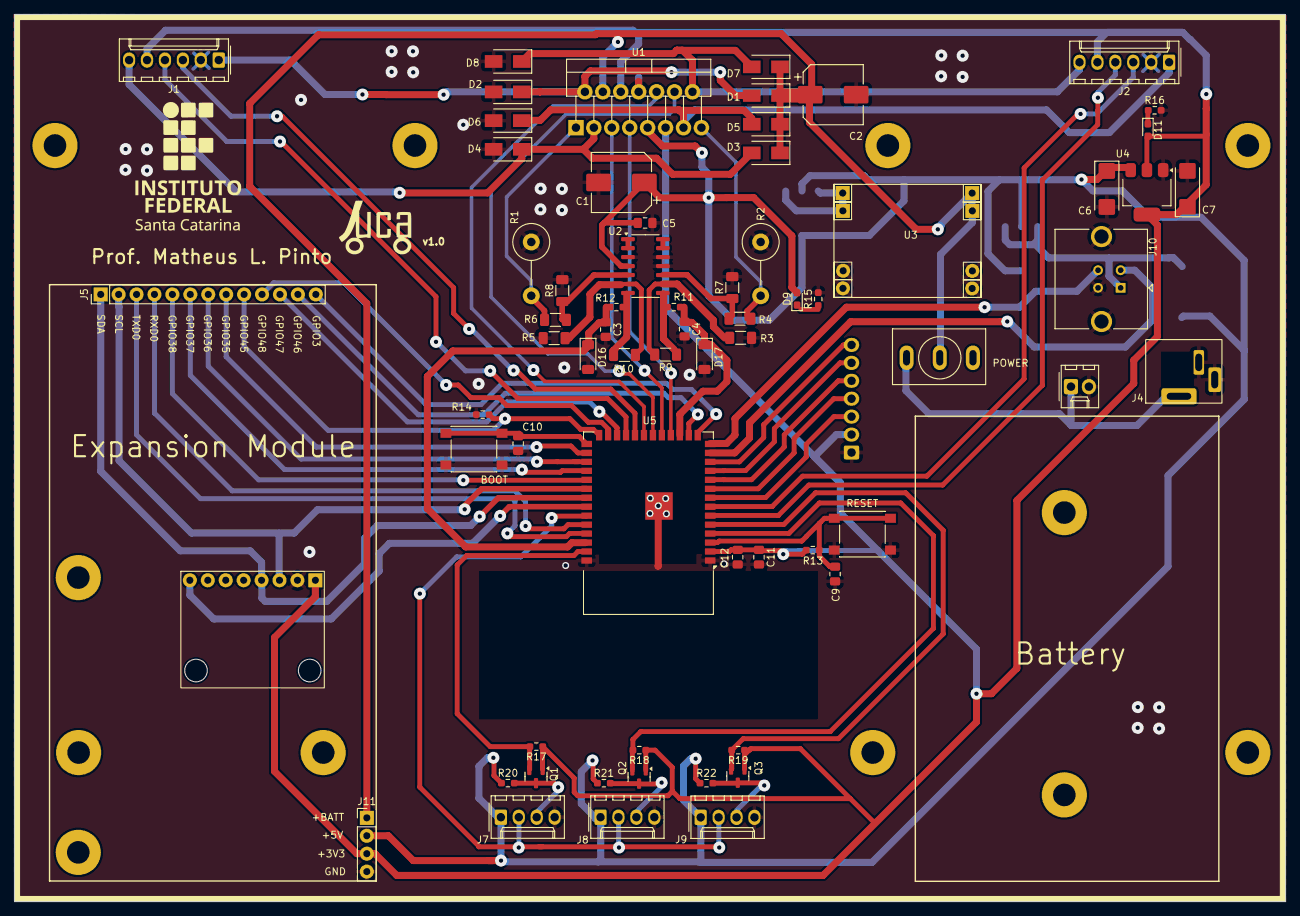
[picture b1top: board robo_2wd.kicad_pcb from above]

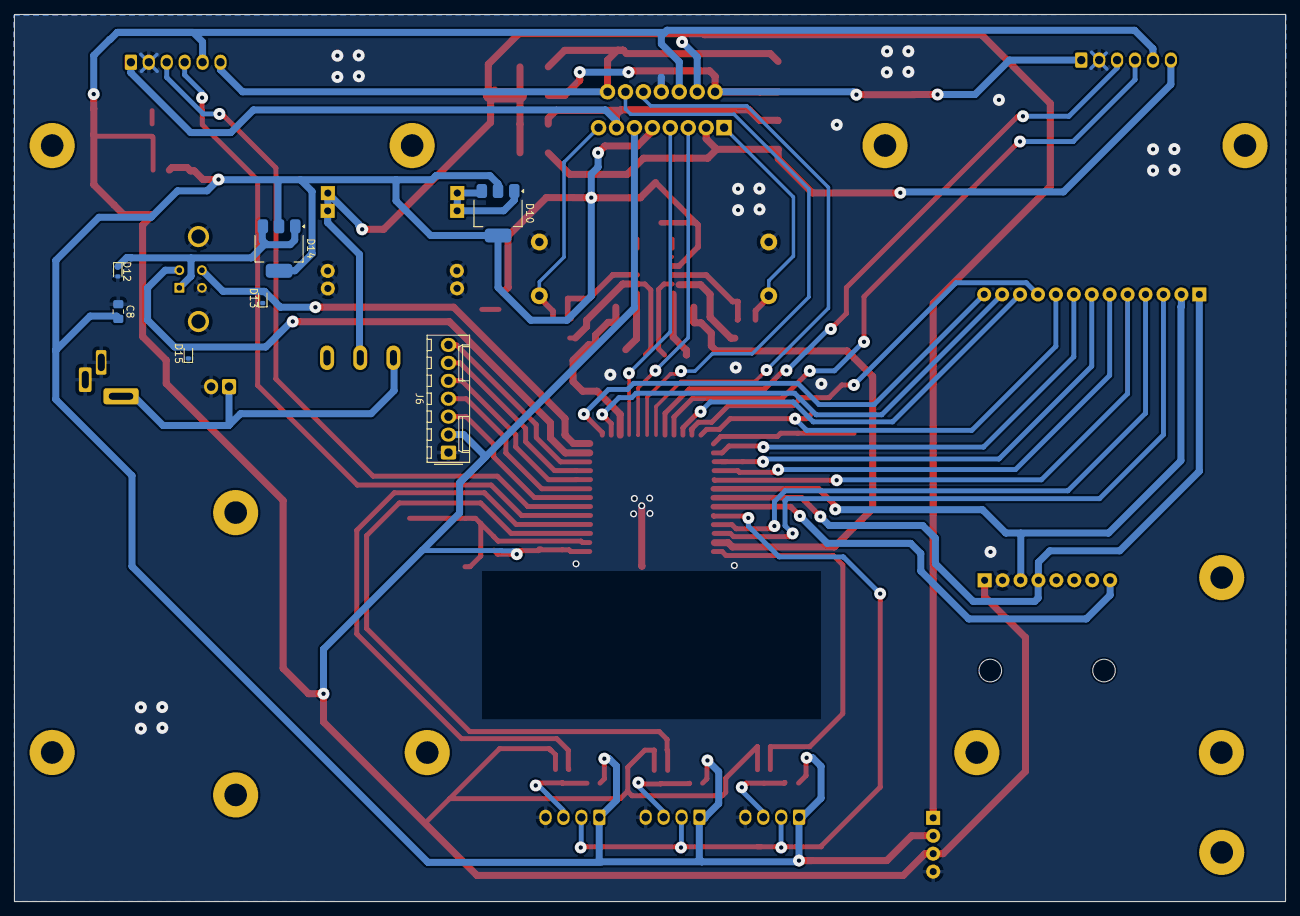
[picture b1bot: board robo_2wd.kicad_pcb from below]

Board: 2 copper layers, 180.1 x 125.7 mm, 74 parts (7 on the bottom side), 63 nets.

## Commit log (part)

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2025-08-25 Add README with project description, structure, and reference
2025-08-25 README adjustments
2026-03-06 Initial code and Kicad
2026-03-18 readme in eletronics and some code
2026-03-18 update in HW doc
    Insertion of current sensor circuit and encoders doc
2026-03-19 break line adjusts
2026-03-19 include managed_components
2026-03-20 Almost end the hw doc + threeeys
2026-03-20 Adjust Juca logo
2026-03-27 Adjust some images back and IR GPIO
2026-04-02 initial motor protect mechanism
2026-04-02 power protection success
2026-04-09 adjust IR pins, Freertos(RTOS), power stall
2026-04-15 adjustment of IR pins
2026-06-11 Corrected wheel.h
    Motor pins and encoder pins inverted
